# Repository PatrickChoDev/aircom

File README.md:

# AirCom - The airbrake module 🚀

## Overview
This PCB is designed for active airbrake control in high-powered rockets, enabling real-time aerodynamic drag adjustments for precise apogee targeting. The system integrates multiple sensors, servo drivers, and comprehensive data logging capabilities.

## Core Features 📌

### Microcontroller & Processing
- STM32G431RBTx (Cortex-M4 with FPU, 170MHz)
- Timer Configuration:
  - TIM2, TIM4, TIM16, TIM17 for servo PWM control
  - Multiple communication interfaces (SPI, I²C, UART)
- Dual Operation Modes:
  - Flight Mode: Autonomous airbrake control
  - USB Configuration Mode: Apogee setup & telemetry access

### Sensor Suite 🔧
- IMU: BMI088 (SPI) - 6-DOF accelerometer & gyroscope
- Altimeter: MS5607 (SPI) - High-precision barometric sensing
- Magnetometer: MMC5983MA (I²C) - Orientation tracking
- Temperature: TMP275 (I²C) - System thermal monitoring

### Control Systems ⚙️
- 4x Servo Motor Outputs (PWM)
  - Independent flap control for roll, yaw, pitch, and drag
  - 3.3V to 5V level shifting via SN74HCT125DR
- Level Shifting Implementation:
  - SN74HCT125DR buffer
  - 2N7002 MOSFETs

### Data Management 💾
- Storage: W25Q256 NOR Flash (256Mbit)
  - 500Hz flight data logging
  - Complete telemetry storage
- USB-C Interface (C169130)
  - Virtual COM Port for configuration
  - Real-time telemetry access

### Power Architecture ⚡
- Dual Power Sources:
  - Battery: 3-17V input (TPS62153 buck converter to 5V)
  - USB-C: 5V VBUS
- Automatic Source Selection: NRVB120VLSFT1G Schottky diodes
- Voltage Regulation:
  - TPS62153: 5V, 1A buck regulator for servos
  - LP5912: 3.3V LDO for core systems

### Protection Features 🛡️
- Reverse Battery Protection
- USB ESD Protection (USBLC6-2SC6)
- Optimized Component Layout:
  - Strategic decoupling capacitor placement
  - Minimal SPI/I²C trace lengths

## Performance Specifications ✨
- 500Hz data sampling and logging
- Reliable servo control system
- Seamless power source switching
- Ruggedized design for high-G environments

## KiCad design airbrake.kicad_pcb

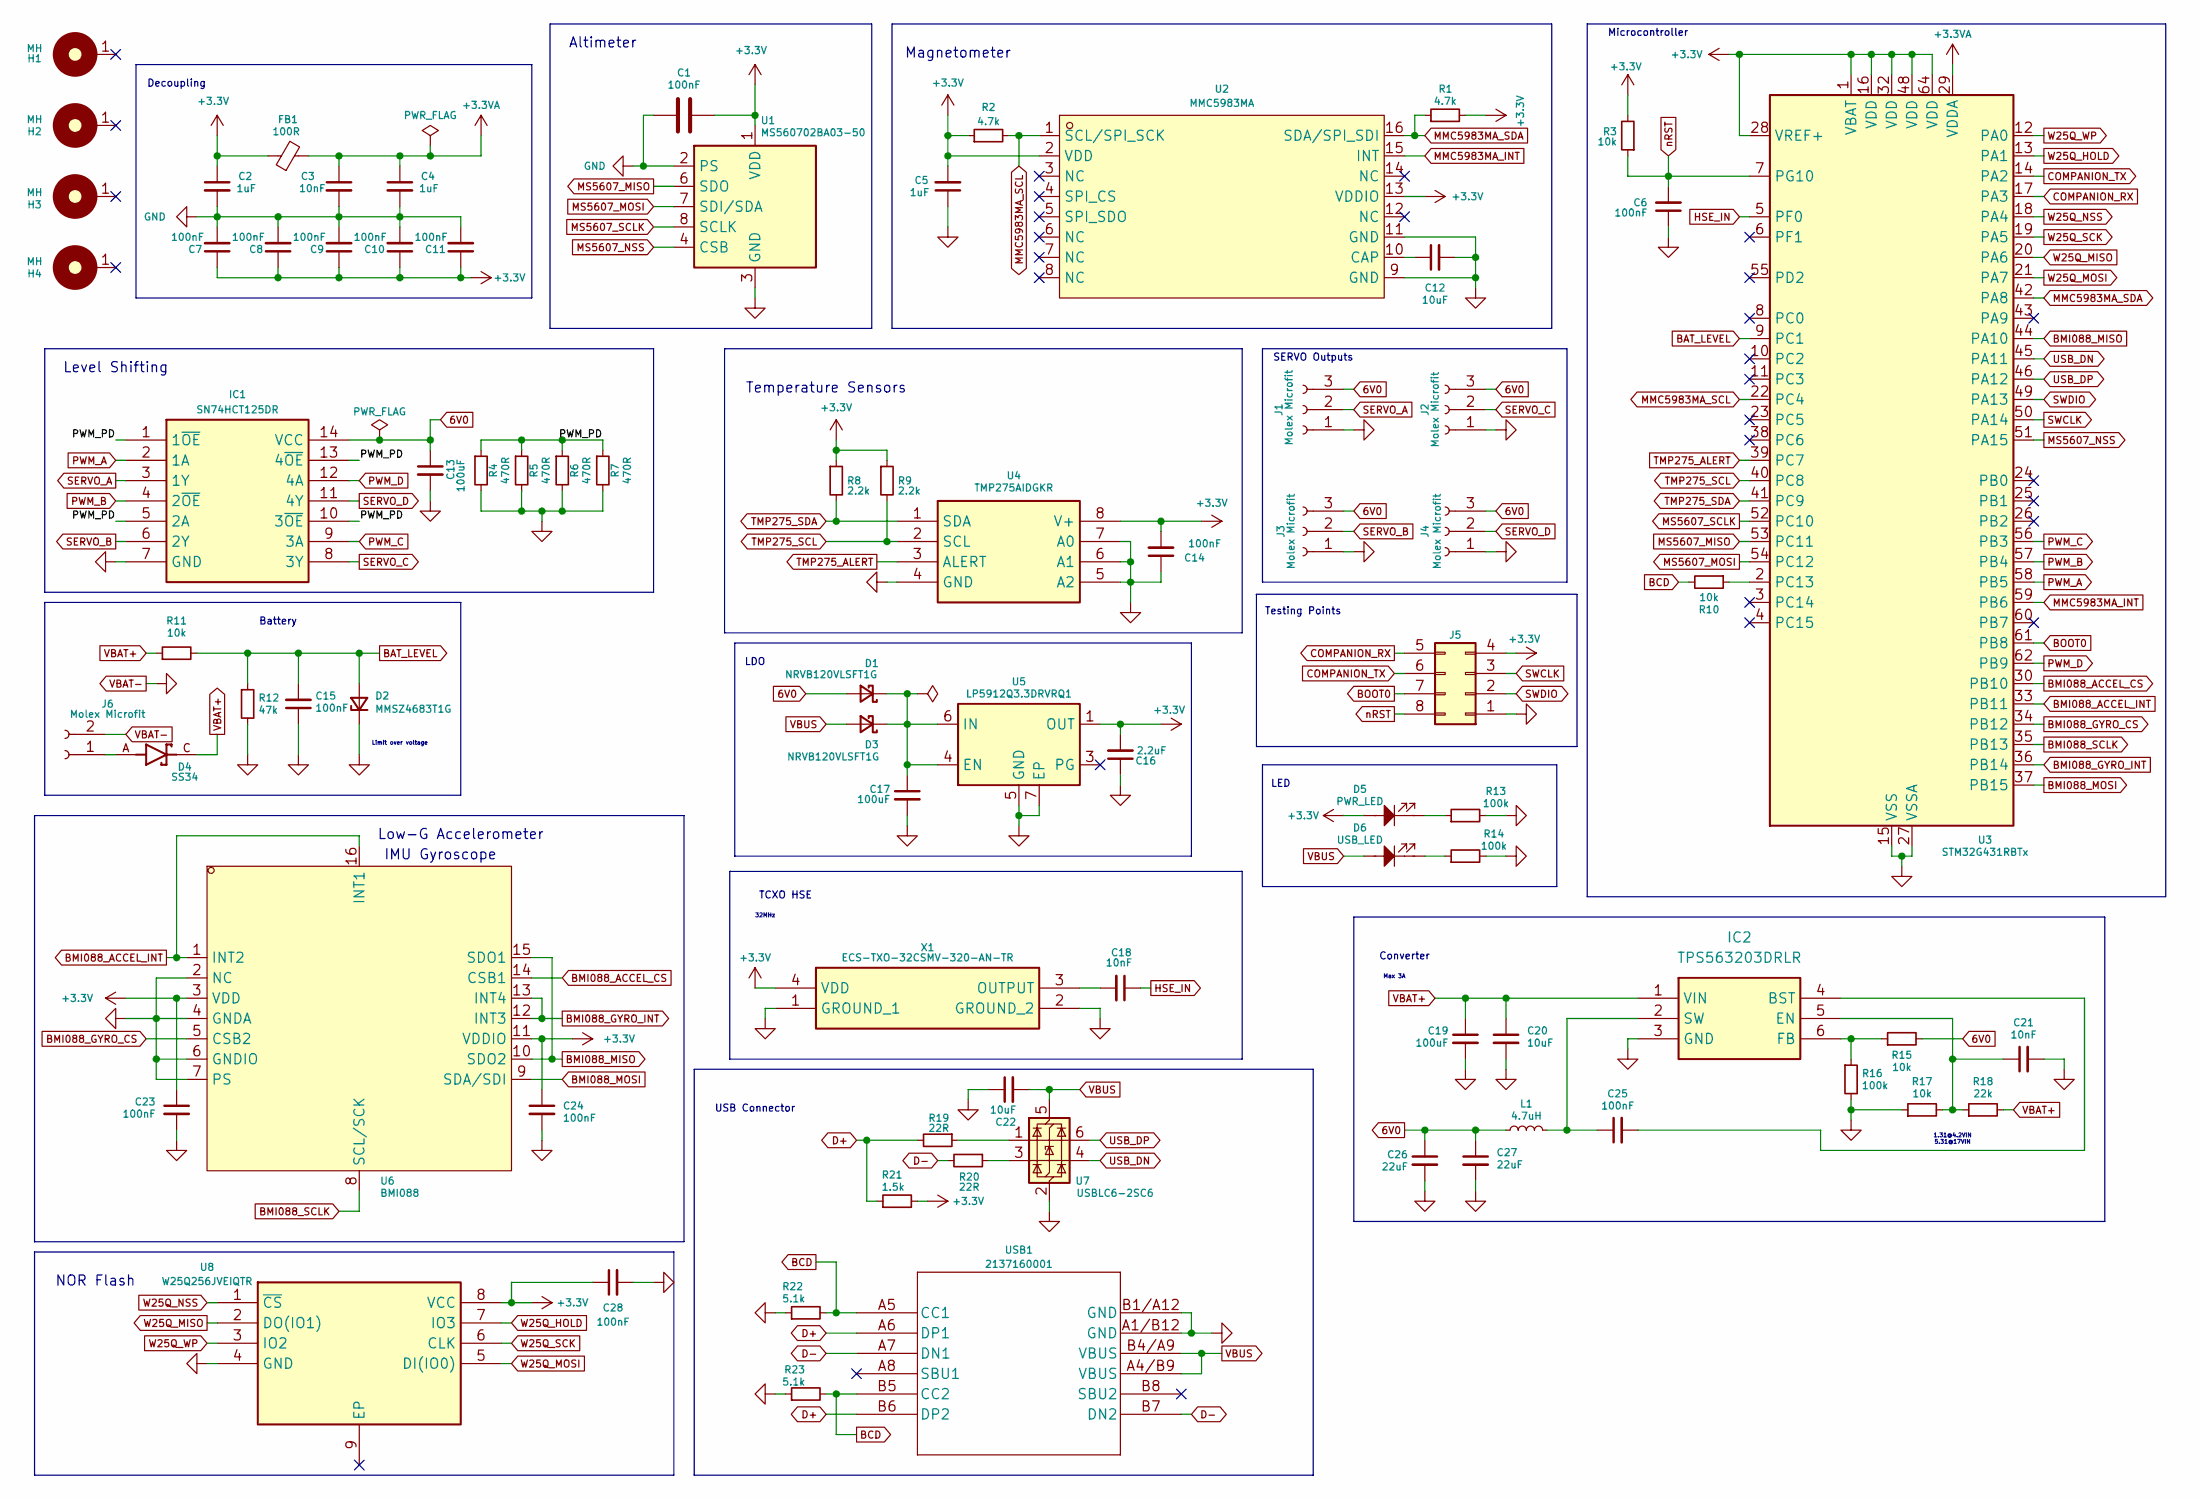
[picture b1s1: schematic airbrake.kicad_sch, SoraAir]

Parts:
C1, C6, C7, C8, C9, C10, C11, C14, C15, C23, C24, C25, C28: 100nF; C_0402_1005Metric_Pad0.74x0.62mm_HandSolder
C2, C4, C5: 1uF; C_0402_1005Metric_Pad0.74x0.62mm_HandSolder
C3, C18, C21: 10nF; C_0402_1005Metric_Pad0.74x0.62mm_HandSolder
C12, C20, C22: 10uF; C_0402_1005Metric_Pad0.74x0.62mm_HandSolder
C13, C17, C19: 100uF; C_1206_3216Metric_Pad1.33x1.80mm_HandSolder
C16: 2.2uF; C_0402_1005Metric_Pad0.74x0.62mm_HandSolder
C26, C27: 22uF; C_0402_1005Metric_Pad0.74x0.62mm_HandSolder
D1, D3: NRVB120VLSFT1G; SODFL3616X98N; Manufacturer_Part_Number NRVB120VLSFT1G; Mouser 863-NRVB120VLSFT1G
D2: MMSZ4683T1G; SOD3716X135N; Manufacturer_Part_Number MMSZ4683T1G; Mouser Part Number 863-MMSZ4683T1G
D4: SS34; DIOM7959X265N; PARTREV 31 Aug 2016
D5: PWR_LED; LED_0402_1005Metric_Pad0.77x0.64mm_HandSolder
D6: USB_LED; LED_0402_1005Metric_Pad0.77x0.64mm_HandSolder
FB1: 100R; L_0603_1608Metric_Pad1.05x0.95mm_HandSolder
H1, H2, H3, H4: MH; MountingHole_3.2mm_Pad
IC1: SN74HCT125DR; SOIC127P600X175-14N; Mouser Part Number 595-SN74HCT125DR
IC2: TPS563203DRLR; SOTFL50P160X60-6N; Manufacturer_Part_Number TPS563203DRLR; Mouser Part Number 595-TPS563203DRLR
J1, J2, J3, J4: Molex Microfit; Molex_Micro-Fit_3.0_43650-0315_1x03_P3.00mm_Vertical
J5: Conn_02x03_Counter_Clockwise; PinHeader_2x04_P2.54mm_Vertical
J6: Molex Microfit; Molex_Micro-Fit_3.0_43650-0215_1x02_P3.00mm_Vertical
L1: 4.7uH; INDPM5050X400N
R1, R2: 4.7k; R_0402_1005Metric_Pad0.72x0.64mm_HandSolder
R3, R10, R11: 10k; R_0402_1005Metric_Pad0.72x0.64mm_HandSolder
R4, R5, R6, R7: 470R; R_0402_1005Metric_Pad0.72x0.64mm_HandSolder
R8, R9: 2.2k; R_0402_1005Metric
R12: 47k; R_0402_1005Metric_Pad0.72x0.64mm_HandSolder
R13, R14, R16: 100k; L_0402_1005Metric_Pad0.77x0.64mm_HandSolder
R15, R17: 10k; L_0402_1005Metric_Pad0.77x0.64mm_HandSolder
R18: 22k; L_0402_1005Metric_Pad0.77x0.64mm_HandSolder
R19, R20: 22R; R_0402_1005Metric_Pad0.72x0.64mm_HandSolder
R21: 1.5k; R_0402_1005Metric_Pad0.72x0.64mm_HandSolder
R22, R23: 5.1k; R_0402_1005Metric_Pad0.72x0.64mm_HandSolder
U1: MS560702BA03-50; LGA-8_3x5mm_P1.25mm; Manufacturer_Part_Number MS560702BA03-50; Mouser Part Number 824-MS560702BA03-50
U2: MMC5983MA; LCSC Part C404329
U3: STM32G431RBTx; LQFP-64_10x10mm_P0.5mm
U4: TMP275AIDGKR; SOP65P490X110-8N; Manufacturer_Part_Number TMP275AIDGKR; Mouser Part Number 595-TMP275AIDGKR
U5: LP5912Q3.3DRVRQ1; WSON-6-1EP_2x2mm_P0.65mm_EP1x1.6mm_ThermalVias; Manufacturer_Part_Number LP5912Q3.3DRVTQ1; Mouser Part Number 595-LP5912Q3.3DRVTQ1
U6: BMI088; LGA-16_L4.5-W3.0-P0.50-BL; LCSC Part C194919
U7: USBLC6-2SC6; SOT-23-6
U8: W25Q256JVEIQTR; SON127P800X600X80-9N-D; Manufacturer_Part_Number W25Q256JVEIQ TR; LCSC Part C97522
USB1: 2137160001; 2171790001_MOL
X1: ECS-TXO-32CSMV-320-AN-TR; ECSTXO32CSMV320ANTR; Manufacturer_Part_Number ECS-TXO-32CSMV-320-AN-TR; Mouser Part Number 520-TXO32CSMV320ANTR

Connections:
6V0: C13.1, C26.1, C27.1, D1.2 (A), IC1.14 (VCC), J1.3, J2.3, J3.3, J4.3, L1.1, R15.2
+3.3V: C1.2, C2.1, C5.2, C7.1, C8.1, C9.1, C10.1, C11.1, C14.2, C16.2, C23.1, C24.1, C28.1, D5.2, FB1.1, J5.4, R1.2, R2.1, R3.2, R8.1, R9.1, R21.2, U1.1 (VDD), U2.2 (VDD), U2.13 (VDDIO), U3.1 (VBAT), U3.16 (VDD), U3.28 (VREF+), U3.32 (VDD), U3.48 (VDD), U3.64 (VDD), U4.8 (V+), U5.1 (OUT), U6.3 (VDD), U6.11 (VDDIO), U8.8 (VCC), X1.4 (VDD)
+3.3VA: C3.1, C4.1, FB1.2, U3.29 (VDDA)
/PWM_PD: IC1.1 (1~OE), IC1.5 (2A), IC1.10 (3~OE), IC1.13 (4~OE), R4.1, R5.1, R6.1, R7.1
BAT_LEVEL: C15.2, D2.2 (A), R11.2, R12.1, U3.9 (PC1)
BCD: R10.2, R22.2, R23.2, USB1.A5 (CC1), USB1.B5 (CC2)
BMI088_ACCEL_CS: U3.30 (PB10), U6.14 (CSB1)
BMI088_ACCEL_INT: U3.33 (PB11), U6.1 (INT2), U6.16 (INT1)
BMI088_GYRO_CS: U3.34 (PB12), U6.5 (CSB2)
BMI088_GYRO_INT: U3.36 (PB14), U6.12 (INT3), U6.13 (INT4)
BMI088_MISO: U3.44 (PA10), U6.10 (SDO2), U6.15 (SDO1)
BMI088_MOSI: U3.37 (PB15), U6.9 (SDA/SDI)
BMI088_SCLK: U3.35 (PB13), U6.8 (SCL/SCK)
BOOT0: J5.7, U3.61 (PB8)
COMPANION_RX: J5.5, U3.17 (PA3)
COMPANION_TX: J5.6, U3.14 (PA2)
D+: R19.2, R21.1, USB1.A6 (DP1), USB1.B6 (DP2)
D-: R20.2, USB1.A7 (DN1), USB1.B7 (DN2)
HSE_IN: C18.1, U3.5 (PF0)
MMC5983MA_INT: U2.15 (INT), U3.59 (PB6)
MMC5983MA_SCL: R2.2, U2.1 (SCL/SPI_SCK), U3.22 (PC4)
MMC5983MA_SDA: R1.1, U2.16 (SDA/SPI_SDI), U3.42 (PA8)
MS5607_MISO: U1.6 (SDO), U3.53 (PC11)
MS5607_MOSI: U1.7 (SDI/SDA), U3.54 (PC12)
MS5607_NSS: U1.4 (CSB), U1.5 (CSB), U3.51 (PA15)
MS5607_SCLK: U1.8 (SCLK), U3.52 (PC10)
unnamed: C17.1, D1.1 (K), D3.1 (K), U5.4 (EN), U5.6 (IN)
unnamed: D5.1, R13.1
unnamed: D6.1, R14.1
unnamed: C25.2, IC2.4 (BST)
unnamed: C21.1, IC2.5 (EN), R17.2, R18.1
unnamed: IC2.6 (FB), R15.1, R16.1
unnamed: C25.1, IC2.2 (SW), L1.2
unnamed: D4.A, J6.1
unnamed: R19.1, U7.1 (I/O1)
unnamed: R20.1, U7.3 (I/O2)
unnamed: C12.1, U2.10 (CAP)
unnamed: R10.1, U3.2 (PC13)
unnamed: C18.2, X1.3 (OUTPUT)
PWM_A: IC1.2 (1A), U3.58 (PB5)
PWM_B: IC1.4 (2~OE), U3.57 (PB4)
PWM_C: IC1.9 (3A), U3.56 (PB3)
PWM_D: IC1.12 (4A), U3.62 (PB9)
SERVO_A: IC1.3 (1Y), J1.2
SERVO_B: IC1.6 (2Y), J3.2
SERVO_C: IC1.8 (3Y), J2.2
SERVO_D: IC1.11 (4Y), J4.2
SWCLK: J5.3, U3.50 (PA14)
SWDIO: J5.2, U3.49 (PA13)
TMP275_ALERT: U3.39 (PC7), U4.3 (ALERT)
TMP275_SCL: R9.2, U3.40 (PC8), U4.2 (SCL)
TMP275_SDA: R8.2, U3.41 (PC9), U4.1 (SDA)
USB_DN: U3.45 (PA11), U7.4 (I/O2)
USB_DP: U3.46 (PA12), U7.6 (I/O1)
VBAT+: C19.1, C20.1, D4.C, IC2.1 (VIN), R11.1, R18.2
VBAT-: C1.1, C2.2, C3.2, C4.2, C5.1, C6.1, C7.2, C8.2, C9.2, C10.2, C11.2, C12.2, C13.2, C14.1, C15.1, C16.1, C17.2, C19.2, C20.2, C21.2, C22.1, C23.2, C24.2, C26.2, C27.2, C28.2, D2.1 (K), IC1.7 (GND), IC2.3 (GND), J1.1, J2.1, J3.1, J4.1, J5.1, J6.2, R4.2, R5.2, R6.2, R7.2, R12.2, R13.2, R14.2, R16.2, R17.1, R22.1, R23.1, U1.2 (PS), U1.3 (GND), U2.9 (GND), U2.11 (GND), U3.15 (VSS), U3.27 (VSSA), U3.31 (VSS), U3.47 (VSS), U3.63 (VSS), U4.4 (GND), U4.5 (A2), U4.6 (A1), U4.7 (A0), U5.5 (GND), U5.7 (EP), U6.2 (NC), U6.4 (GNDA), U6.6 (GNDIO), U6.7 (PS), U7.2 (GND), U8.4 (GND), USB1.A1/B12 (GND), USB1.B1/A12 (GND), X1.1 (GROUND_1), X1.2 (GROUND_2)
VBUS: C22.2, D3.2 (A), D6.2, U7.5 (VBUS), USB1.A4/B9 (VBUS), USB1.B4/A9 (VBUS)
W25Q_HOLD: U3.13 (PA1), U8.7 (IO3)
W25Q_MISO: U3.20 (PA6), U8.2 (DO(IO1))
W25Q_MOSI: U3.21 (PA7), U8.5 (DI(IO0))
W25Q_NSS: U3.18 (PA4), U8.1 (~CS)
W25Q_SCK: U3.19 (PA5), U8.6 (CLK)
W25Q_WP: U3.12 (PA0), U8.3 (IO2)
nRST: C6.2, J5.8, R3.1, U3.7 (PG10)

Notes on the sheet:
Battery
Level Shifting
Magnetometer
Converter
32MHz
Decoupling
USB Connector
SERVO Outputs
Altimeter
Low-G Accelerometer
Testing Points
IMU Gyroscope
Microcontroller
TCXO HSE
Temperature Sensors
NOR Flash
Max 3A
1.31@4.2VIN 5.31@17VIN
Limit over voltage
LDO
LED

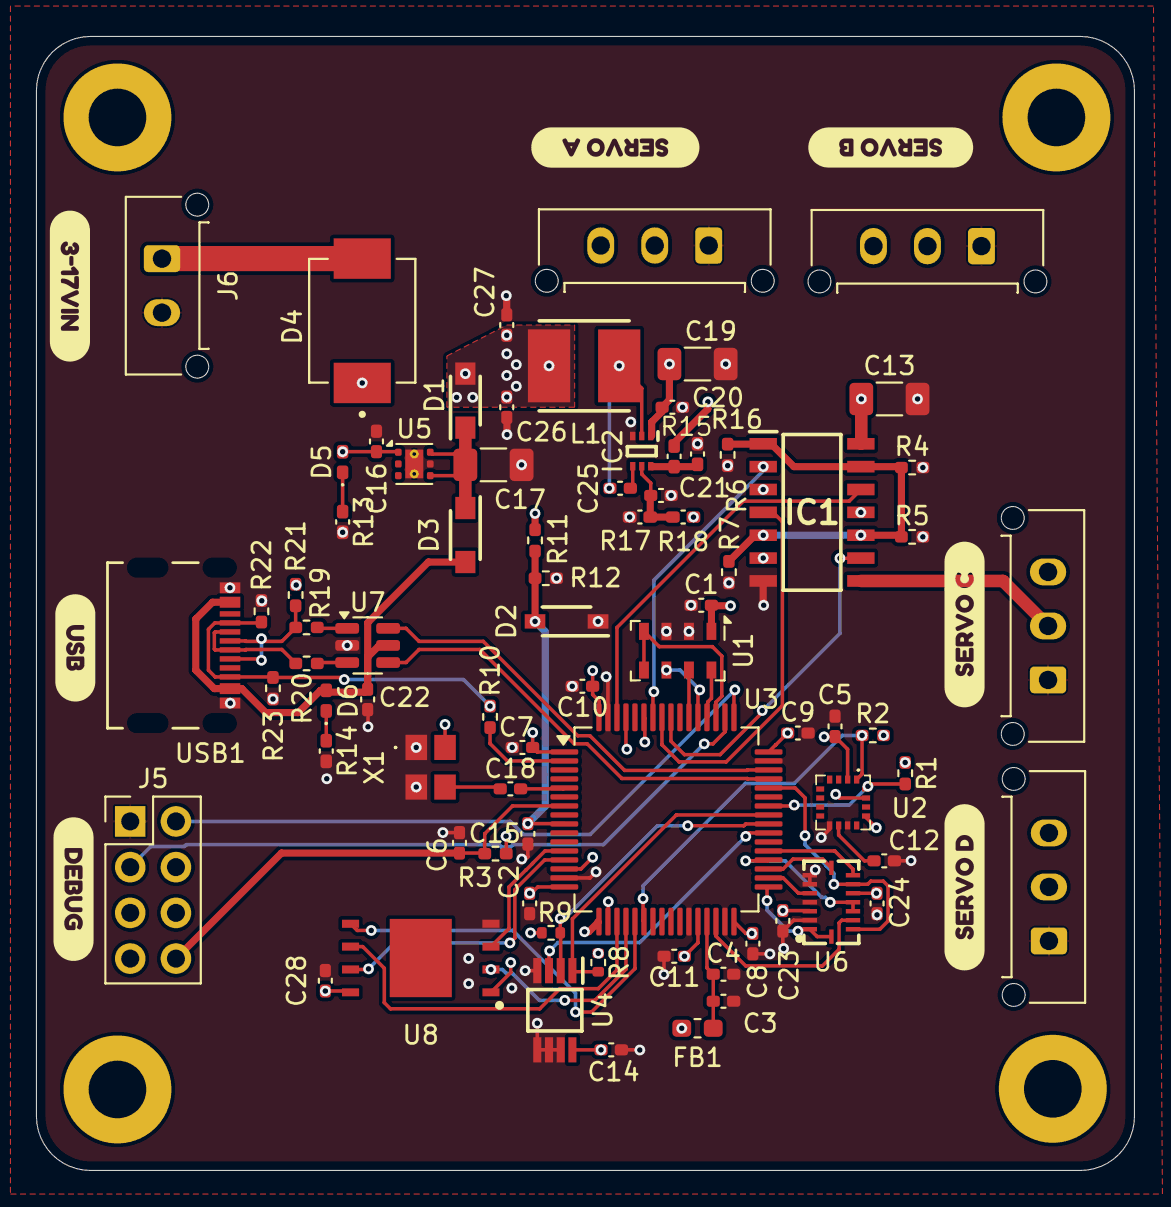
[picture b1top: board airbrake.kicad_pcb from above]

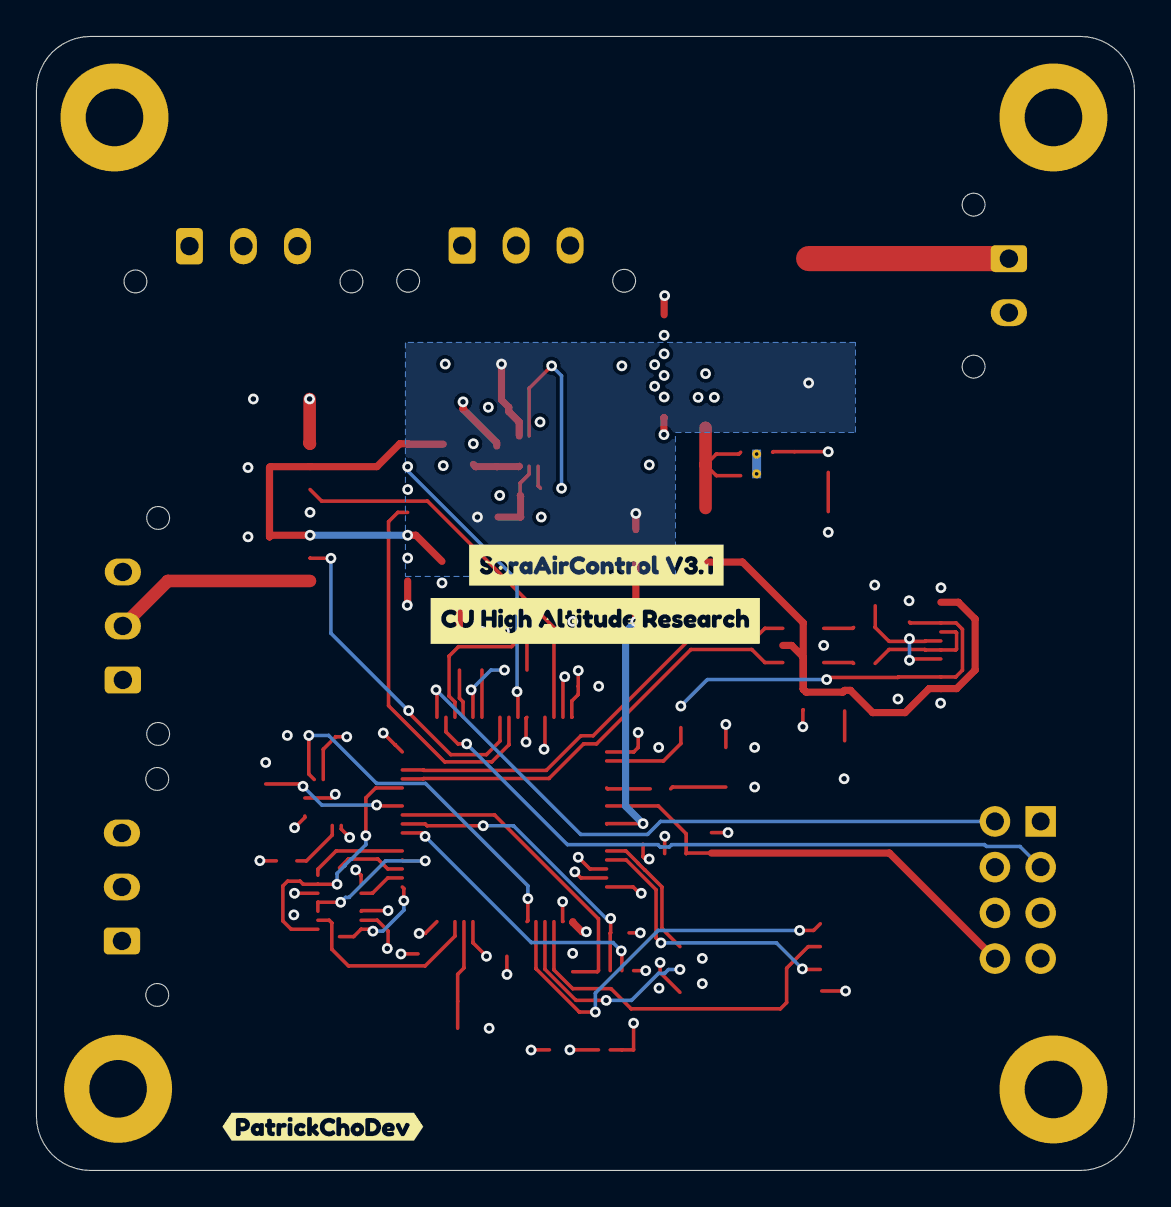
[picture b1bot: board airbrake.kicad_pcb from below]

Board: 4 copper layers, 61.0 x 63.0 mm, 91 parts (3 on the bottom side), 64 nets.

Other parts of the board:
kibuzzard-682EDA3B: G***; kibuzzard-682EDA3B
kibuzzard-682EDA9B: G***; kibuzzard-682EDA9B
kibuzzard-682EDA42: G***; kibuzzard-682EDA42
kibuzzard-682EDAA9: G***; kibuzzard-682EDAA9
kibuzzard-682EDAC6: G***; kibuzzard-682EDAC6
kibuzzard-682EDAD5: G***; kibuzzard-682EDAD5
kibuzzard-682EDAED: G***; kibuzzard-682EDAED
kibuzzard-682EDBD7: G***; kibuzzard-682EDBD7
kibuzzard-682EDEAD: G***; kibuzzard-682EDEAD
kibuzzard-682EDEC5: G***; kibuzzard-682EDEC5

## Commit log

2025-02-11 chore: init project
2025-02-11 feat(pcb): trace routing
2025-02-13 feat(silscreen): adjust silkscreen and some trace
2025-02-13 feat(via): add stitching
2025-02-13 feat(drawing): renew pdf
2025-02-22 release: rev1
2025-04-22 feat: v1
2025-05-20 feat: v2 schematic
2025-05-22 feat: v3
2025-05-22 feat: v2 modified
2025-06-01 feat: 3.1
